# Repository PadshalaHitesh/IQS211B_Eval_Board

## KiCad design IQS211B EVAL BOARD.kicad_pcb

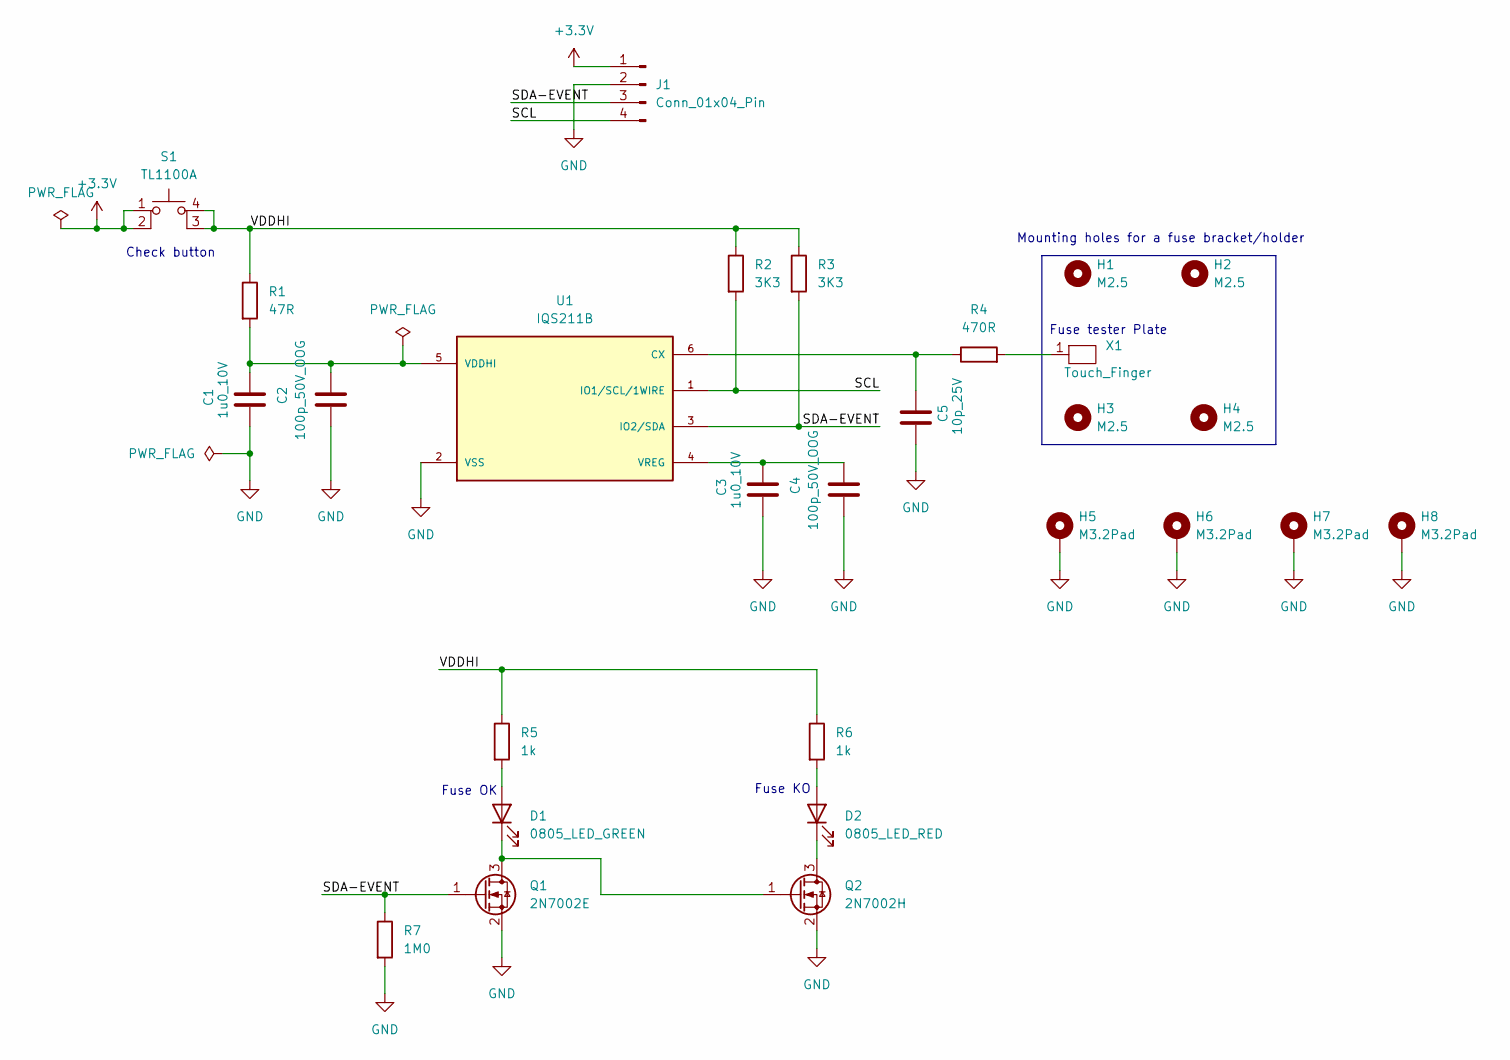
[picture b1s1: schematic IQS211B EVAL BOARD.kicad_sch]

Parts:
C1, C3: 1u0_10V; C_0805_2012Metric
C2, C4: 100p_50V_OOG; C_0805_2012Metric
C5: 10p_25V; C_0805_2012Metric
D1: 0805_LED_GREEN; LED_0805_2012Metric
D2: 0805_LED_RED; LED_0805_2012Metric
H1, H2, H3, H4: M2.5; MountingHole_2.5mm
H5, H6, H7, H8: M3.2Pad; MountingHole_3.2mm_M3_ISO7380_Pad
J1: Conn_01x04_Pin; PinHeader_1x04_P2.54mm_Vertical
Q1: 2N7002E; SOT-23
Q2: 2N7002H; SOT-23
R1: 47R; R_0805_2012Metric
R2, R3: 3K3; R_0805_2012Metric
R4: 470R; R_0805_2012Metric
R5, R6: 1k; R_0805_2012Metric
R7: 1M0; R_0805_2012Metric
S1: TL1100A; SW_MEC_5GSH9
U1: IQS211B; SOT95P280X100-6N; PARTREV 2.4; DigiKey_Part_Number 1790-IQS211B00000000TSRCT-ND
X1: Touch_Finger; Touch_Finger_Circle_10mm

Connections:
+3.3V: J1.1, S1.1, S1.2
/SCL: J1.4, R2.2, U1.1 (IO1/SCL/1WIRE)
/SDA-EVENT: J1.3, Q1.1 (G), R3.2, R7.1, U1.3 (IO2/SDA)
/VDDHI: R1.1, R2.1, R3.1, R5.1, R6.1, S1.3 (K), S1.4 (A)
GND: C1.2, C2.2, C3.2, C4.2, C5.2, H5.1, H6.1, H7.1, H8.1, J1.2, Q1.2 (S), Q2.2 (S), R7.2, U1.2 (VSS)
unnamed: D1.2 (A), R5.2
unnamed: D1.1 (K), Q1.3 (D), Q2.1 (G)
unnamed: D2.2 (A), R6.2
unnamed: D2.1 (K), Q2.3 (D)
unnamed: R4.2, X1.1
unnamed: C5.1, R4.1, U1.6 (CX)
unnamed: C1.1, C2.1, R1.2, U1.5 (VDDHI)
unnamed: C3.1, C4.1, U1.4 (VREG)

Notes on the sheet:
Fuse KO
Fuse tester Plate
Fuse OK
Mounting holes for a fuse bracket/holder
Check button

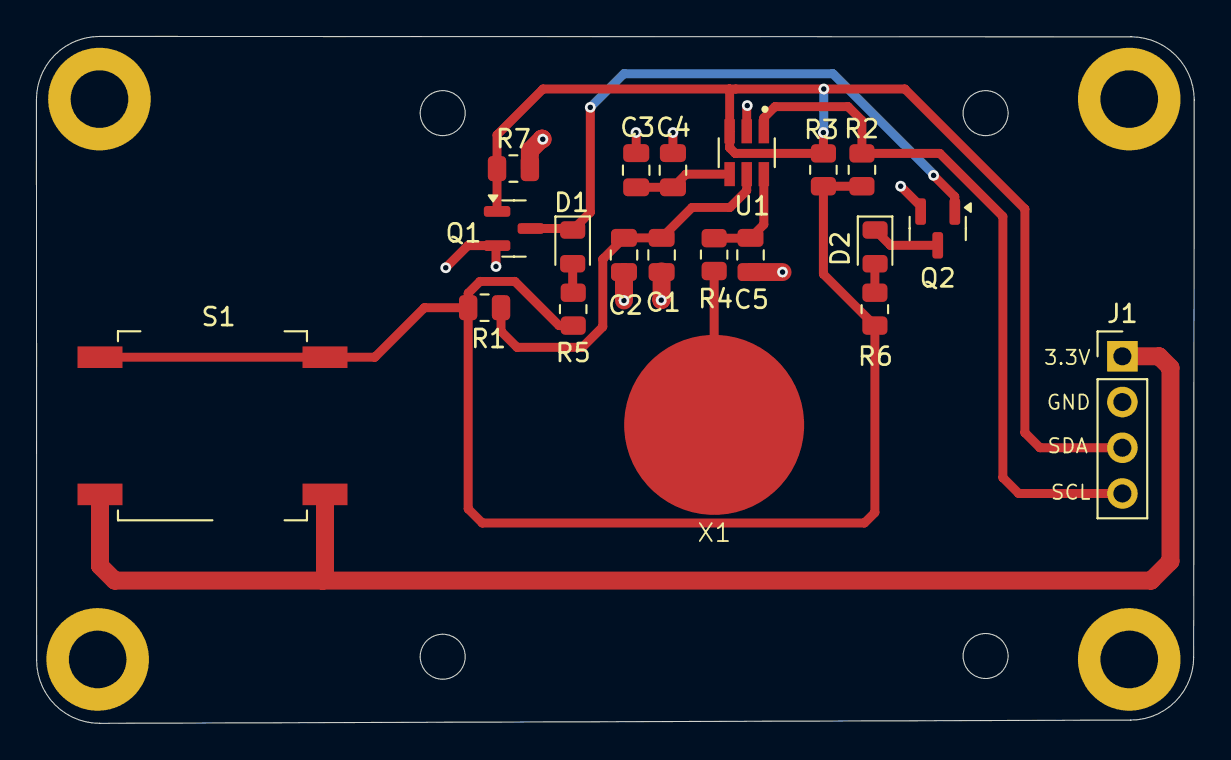
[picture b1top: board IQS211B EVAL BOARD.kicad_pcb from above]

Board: 2 copper layers, 64.3 x 38.2 mm, 28 parts (0 on the bottom side), 13 nets.

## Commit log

2025-08-26 Add files via upload
    completed schematic design.
